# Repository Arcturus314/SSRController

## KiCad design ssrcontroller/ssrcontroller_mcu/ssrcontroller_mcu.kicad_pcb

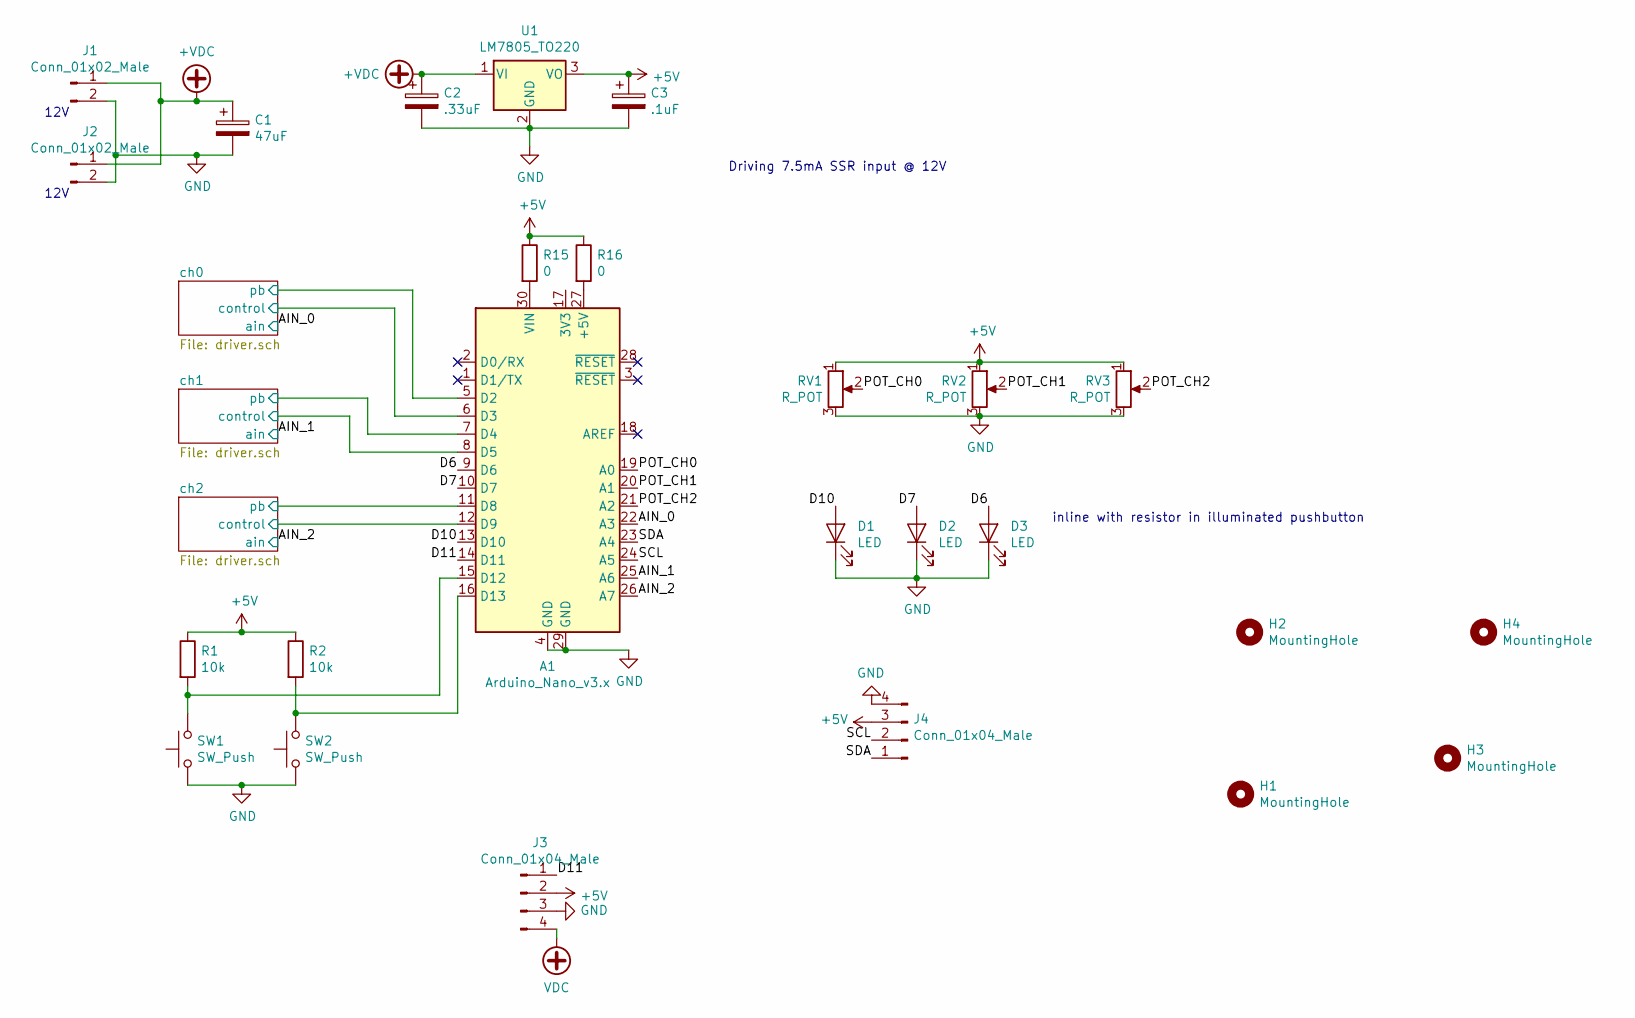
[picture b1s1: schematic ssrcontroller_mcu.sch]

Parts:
A1: Arduino_Nano_v3.x; Arduino_Nano
C1: 47uF; CP_Radial_D5.0mm_P2.00mm
C2: .33uF; CP_Radial_D5.0mm_P2.00mm
C3: .1uF; CP_Radial_D5.0mm_P2.00mm
D1, D2, D3: LED; PinHeader_1x02_P2.54mm_Vertical
H1, H2, H3, H4: MountingHole; MountingHole_3.2mm_M3_DIN965_Pad
J1: Conn_01x02_Male; BarrelJack_Horizontal
J2: Conn_01x02_Male; TerminalBlock_Phoenix_MKDS-1,5-2_1x02_P5.00mm_Horizontal
J3: Conn_01x04_Male; PinHeader_1x04_P2.54mm_Vertical
J4: Conn_01x04_Male; PinSocket_1x04_P2.54mm_Vertical
R1, R2: 10k; R_Axial_DIN0207_L6.3mm_D2.5mm_P7.62mm_Horizontal
R15, R16: 0; R_0603_1608Metric_Pad1.05x0.95mm_HandSolder
RV1, RV2, RV3: R_POT; Potentiometer_Alps_RK09K_Single_Horizontal
SW1, SW2: SW_Push; SW_Tactile_SKHH_Angled
U1: LM7805_TO220; TO-220-3_Horizontal_TabDown

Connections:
+5V: C3.1, J3.2, J4.3, R1.1, R2.1, R15.1, R16.1, RV1.1, RV2.1, RV3.1, U1.3 (VO); also elsewhere on the board
+VDC: C1.1, C2.1, J1.1, J2.1, U1.1 (VI); also elsewhere on the board
/AIN_0: A1.22 (A3); also elsewhere on the board
/AIN_1: A1.25 (A6); also elsewhere on the board
/AIN_2: A1.26 (A7); also elsewhere on the board
/D6: A1.9 (D6), D3.2 (A)
/D7: A1.10 (D7), D2.2 (A)
/D10: A1.13 (D10), D1.2 (A)
/D11: A1.14 (D11), J3.1
/POT_CH0: A1.19 (A0), RV1.2
/POT_CH1: A1.20 (A1), RV2.2
/POT_CH2: A1.21 (A2), RV3.2
/SCL: A1.24 (A5), J4.2
/SDA: A1.23 (A4), J4.1
/ch0/control: A1.6 (D3); also elsewhere on the board
/ch0/pb: A1.5 (D2); also elsewhere on the board
/ch1/control: A1.8 (D5); also elsewhere on the board
/ch1/pb: A1.7 (D4); also elsewhere on the board
/ch2/control: A1.12 (D9); also elsewhere on the board
/ch2/pb: A1.11 (D8); also elsewhere on the board
GND: A1.4 (GND), A1.29 (GND), C1.2, C2.2, C3.2, D1.1 (K), D2.1 (K), D3.1 (K), J1.2, J2.2, J3.3, J4.4, RV1.3, RV2.3, RV3.3, SW1.1, SW2.1, U1.2 (GND); also elsewhere on the board
unnamed: A1.15 (D12), R1.2, SW1.2
unnamed: A1.16 (D13), R2.2, SW2.2
unnamed: A1.27 (+5V), R16.2
unnamed: A1.30 (VIN), R15.2
VDC: J3.4

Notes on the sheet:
Driving 7.5mA SSR input @ 12V
12V
inline with resistor in illuminated pushbutton

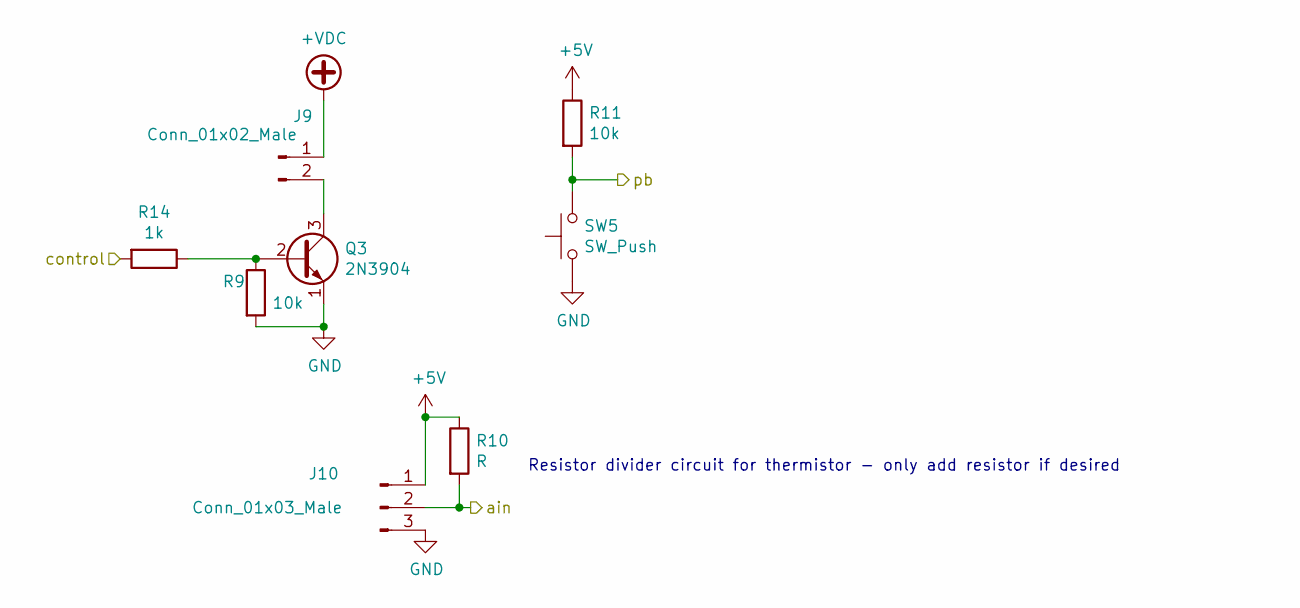
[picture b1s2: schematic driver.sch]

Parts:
J5: Conn_01x02_Male; TerminalBlock_Phoenix_MKDS-1,5-2_1x02_P5.00mm_Horizontal
J6: Conn_01x03_Male; PinHeader_1x03_P2.54mm_Vertical
Q1: 2N3904; TO-92_Inline
R3, R5: 10k; R_Axial_DIN0207_L6.3mm_D2.5mm_P7.62mm_Horizontal
R4: R; R_Axial_DIN0207_L6.3mm_D2.5mm_P7.62mm_Horizontal
R12: 1k; R_Axial_DIN0207_L6.3mm_D2.5mm_P7.62mm_Horizontal
SW3: SW_Push; SW_Tactile_SKHH_Angled

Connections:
+5V: J6.1, R4.1, R5.1; also elsewhere on the board
+VDC: J5.1; also elsewhere on the board
/AIN_0: J6.2, R4.2; also elsewhere on the board
/ch0/control: R12.2; also elsewhere on the board
/ch0/pb: R5.2, SW3.2; also elsewhere on the board
GND: J6.3, Q1.1 (E), R3.2, SW3.1; also elsewhere on the board
unnamed: J5.2, Q1.3 (C)
unnamed: Q1.2 (B), R3.1, R12.1

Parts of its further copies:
J7, J9: Conn_01x02_Male; TerminalBlock_Phoenix_MKDS-1,5-2_1x02_P5.00mm_Horizontal
J8, J10: Conn_01x03_Male; PinHeader_1x03_P2.54mm_Vertical
Q2, Q3: 2N3904; TO-92_Inline
R6, R8, R9, R11: 10k; R_Axial_DIN0207_L6.3mm_D2.5mm_P7.62mm_Horizontal
R7, R10: R; R_Axial_DIN0207_L6.3mm_D2.5mm_P7.62mm_Horizontal
R13, R14: 1k; R_Axial_DIN0207_L6.3mm_D2.5mm_P7.62mm_Horizontal
SW4, SW5: SW_Push; SW_Tactile_SKHH_Angled

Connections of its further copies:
+5V: J8.1, J10.1, R7.1, R8.1, R10.1, R11.1; also elsewhere on the board
+VDC: J7.1, J9.1; also elsewhere on the board
/AIN_1: J8.2, R7.2; also elsewhere on the board
/AIN_2: J10.2, R10.2; also elsewhere on the board
/ch1/control: R13.2; also elsewhere on the board
/ch1/pb: R8.2, SW4.2; also elsewhere on the board
/ch2/control: R14.2; also elsewhere on the board
/ch2/pb: R11.2, SW5.2; also elsewhere on the board
GND: J8.3, J10.3, Q2.1 (E), Q3.1 (E), R6.2, R9.2, SW4.1, SW5.1; also elsewhere on the board
unnamed: J7.2, Q2.3 (C)
unnamed: J9.2, Q3.3 (C)
unnamed: Q2.2 (B), R6.1, R13.1
unnamed: Q3.2 (B), R9.1, R14.1

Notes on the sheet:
Resistor divider circuit for thermistor - only add resistor if desired

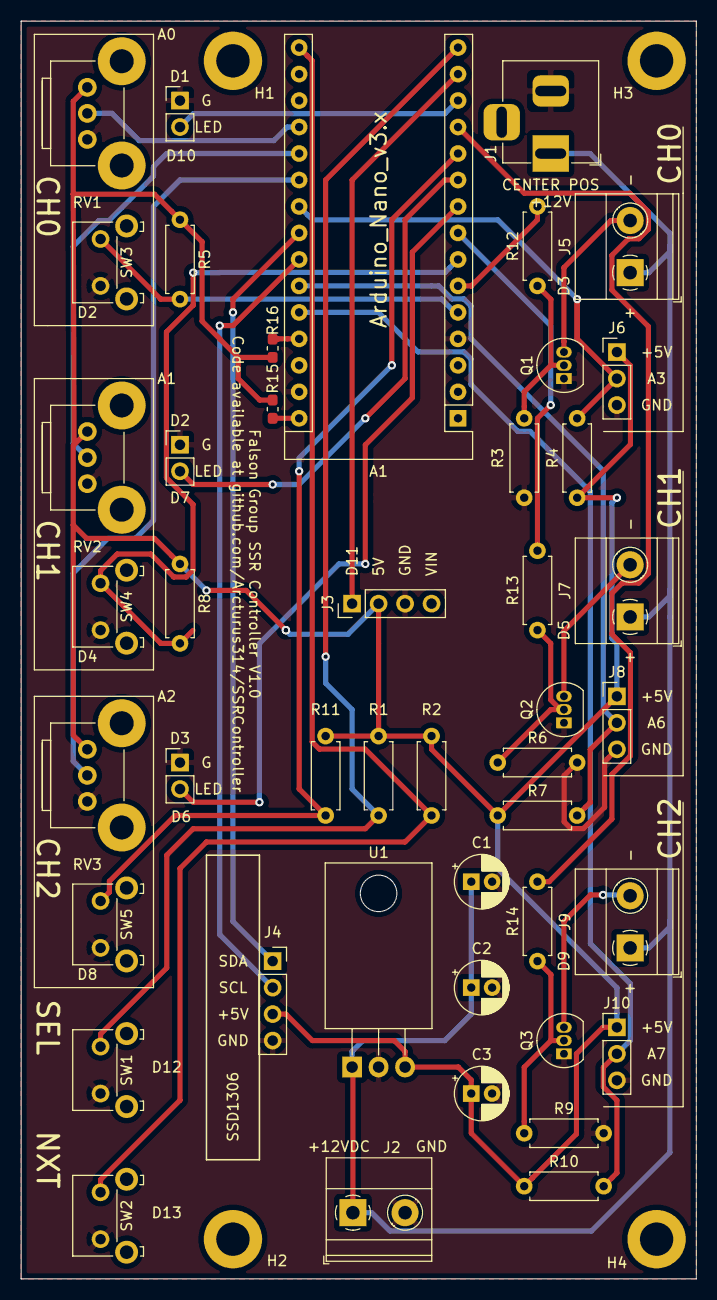
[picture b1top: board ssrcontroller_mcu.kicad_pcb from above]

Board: 2 copper layers, 64.8 x 120.7 mm, 49 parts (0 on the bottom side), 31 nets.

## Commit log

2021-03-29 added pinout
2021-03-30 added simple first-draft implementation
2021-03-31 added BoMs
2021-04-02 updated BoM
2021-04-02 updated Mouser BoM
2021-04-16 updates as per 4/16/2021 meeting
2021-04-17 added Amazon BoM without spares
2021-04-24 Added standoffs to BoM
2021-08-17 added pcb files
